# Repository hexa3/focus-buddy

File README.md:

# Focus Buddy

An e-ink Pomodoro companion for your desk. A little tomato with a face counts down your focus blocks on a
2.9" e-paper screen, chimes when you're done, and naps when you walk away.

- **Seeed XIAO ESP32-C3** + **Waveshare 2.9" e-paper** (296×128)
- 3 buttons, buzzer, optional LiPo with battery gauge
- **All through-hole**, 18 parts, about 2 h to build
- Light sleep between screen updates; deep sleep (≈0.05 mA) after 3 min idle. E-ink keeps the image with zero power.

## Pictures

> No unit has been built yet, so these aren't photos. Each one comes straight from the project files:
> KiCad renders and exports, the real enclosure geometry, and screens drawn by the actual firmware in the desktop simulator.

**The screens:** every state, drawn by `firmware/src/ui.cpp`

**The PCB:** 106 × 64 mm, 2 layers, all through-hole (KiCad 3D render)

**Routing:** back copper layer, seen from behind (KiCad export)

**The case:** front shell, PCB, back cover and button caps, exploded (rendered from the OpenSCAD model)

**The schematic** (KiCad export)

**The buddy talks:** speech bubble added in the latest display update (before / after, real firmware output)

## What's in here

This repo holds **source files only**. Gerbers, STLs, STEP, PDFs, renders and videos are generated from them
(see "Generate the outputs" below) and are not committed.

| Path | What |
|---|---|
| [`docs/BUILD.md`](docs/BUILD.md) | **Start here.** Ordering, printing, soldering, flashing, assembly, troubleshooting |
| [`hardware/BOM.csv`](hardware/BOM.csv) | **Everything you need:** PCB parts, display, screws, printed parts, filament, solder, tools, software (generated by `tools/gen_bom.py`) |
| `tools/netlist.py` | **Single source of truth:** every part, net and its position on the board |
| `hardware/pcb/` | KiCad 9 project: `.kicad_pro`, `.kicad_sch`, `.kicad_pcb`, project symbol and footprint libraries |
| `hardware/cad/enclosure.scad` | Parametric OpenSCAD source of the case (front shell, back cover, button caps, stand) |
| `hardware/cad/pcb_positions.scad` | Hole and switch positions taken from the PCB (generated by `tools/gen_cad_params.py`) |
| `firmware/` | PlatformIO firmware (Arduino/ESP32, GxEPD2). All screen drawing is in `src/ui.cpp` |
| `sim/` | Desktop simulator: compiles `ui.cpp` for your PC and renders the real screens |
| `tools/` | `build_pcb.py` (place + ground pour), `route_pcb.py` (A* autorouter), `build_schematic.py`, `gen_bom.py`, `gen_cad_params.py`, `render_stl.py`, `make_all.sh` |
| `video/` | Scripts that render the progress reels and before/after clips from simulator output |

## Generate the outputs

```bash
tools/make_all.sh
```

This needs Docker (it uses the `kicad/kicad:9.0` and `openscad/openscad:2021.01` images) and runs at low priority on 1 CPU.
It writes:

| Output | Path |
|---|---|
| Gerbers + drill files (upload the zip to a PCB fab) | `hardware/fab/focus-buddy-gerbers.zip` |
| Schematic PDF | `hardware/fab/focus-buddy-schematic.pdf` |
| PCB STEP model, 3D renders, part positions | `hardware/fab/` |
| Printable STLs | `hardware/cad/stl/` |
| DRC / ERC reports | `hardware/pcb/*.rpt` |

## Quick start

```bash
# 1. firmware
cd firmware && pio run -t upload

# 2. preview the screens without hardware
pio run                       # once, to fetch the graphics library
../sim/build.sh
../sim/fbsim main 1 0 1 1380000 1500000 2 2 37 0 3900 "Classic 25/5" 25 /tmp/screen.pbm

# 3. regenerate all hardware outputs (docker; low priority, 1 CPU)
tools/make_all.sh
```

## Verification status

| Check | Result |
|---|---|
| Firmware build, 4 panel variants | ✅ compiles (≈23 % flash, 6 % RAM) |
| Schematic ERC | ✅ 0 errors |
| PCB DRC | ✅ 0 errors, 0 unconnected |
| Schematic ↔ PCB parity | ✅ 0 issues |
| Enclosure STLs | ✅ manifold (OpenSCAD "Simple: yes") |
| **Built and tested on real hardware** | ❌ **not yet.** Rev A is unbuilt; see the checklist in BUILD.md |

The repo-wide DRC/ERC reports also list "library not in global table" notes. Those come from the bare docker
image used for CI, not from the design.

## License

Suggested: hardware CERN-OHL-P v2, firmware and tools MIT. These were picked as sensible open defaults; change them before publishing if you prefer something else.

---

<p align="center"><sub><i>Disclaimer: this README was generated by AI. I'm honestly terrible at describing my own projects (my first draft is usually just "it does the thing, trust me"), so I let a robot do the explaining.</i></sub></p>

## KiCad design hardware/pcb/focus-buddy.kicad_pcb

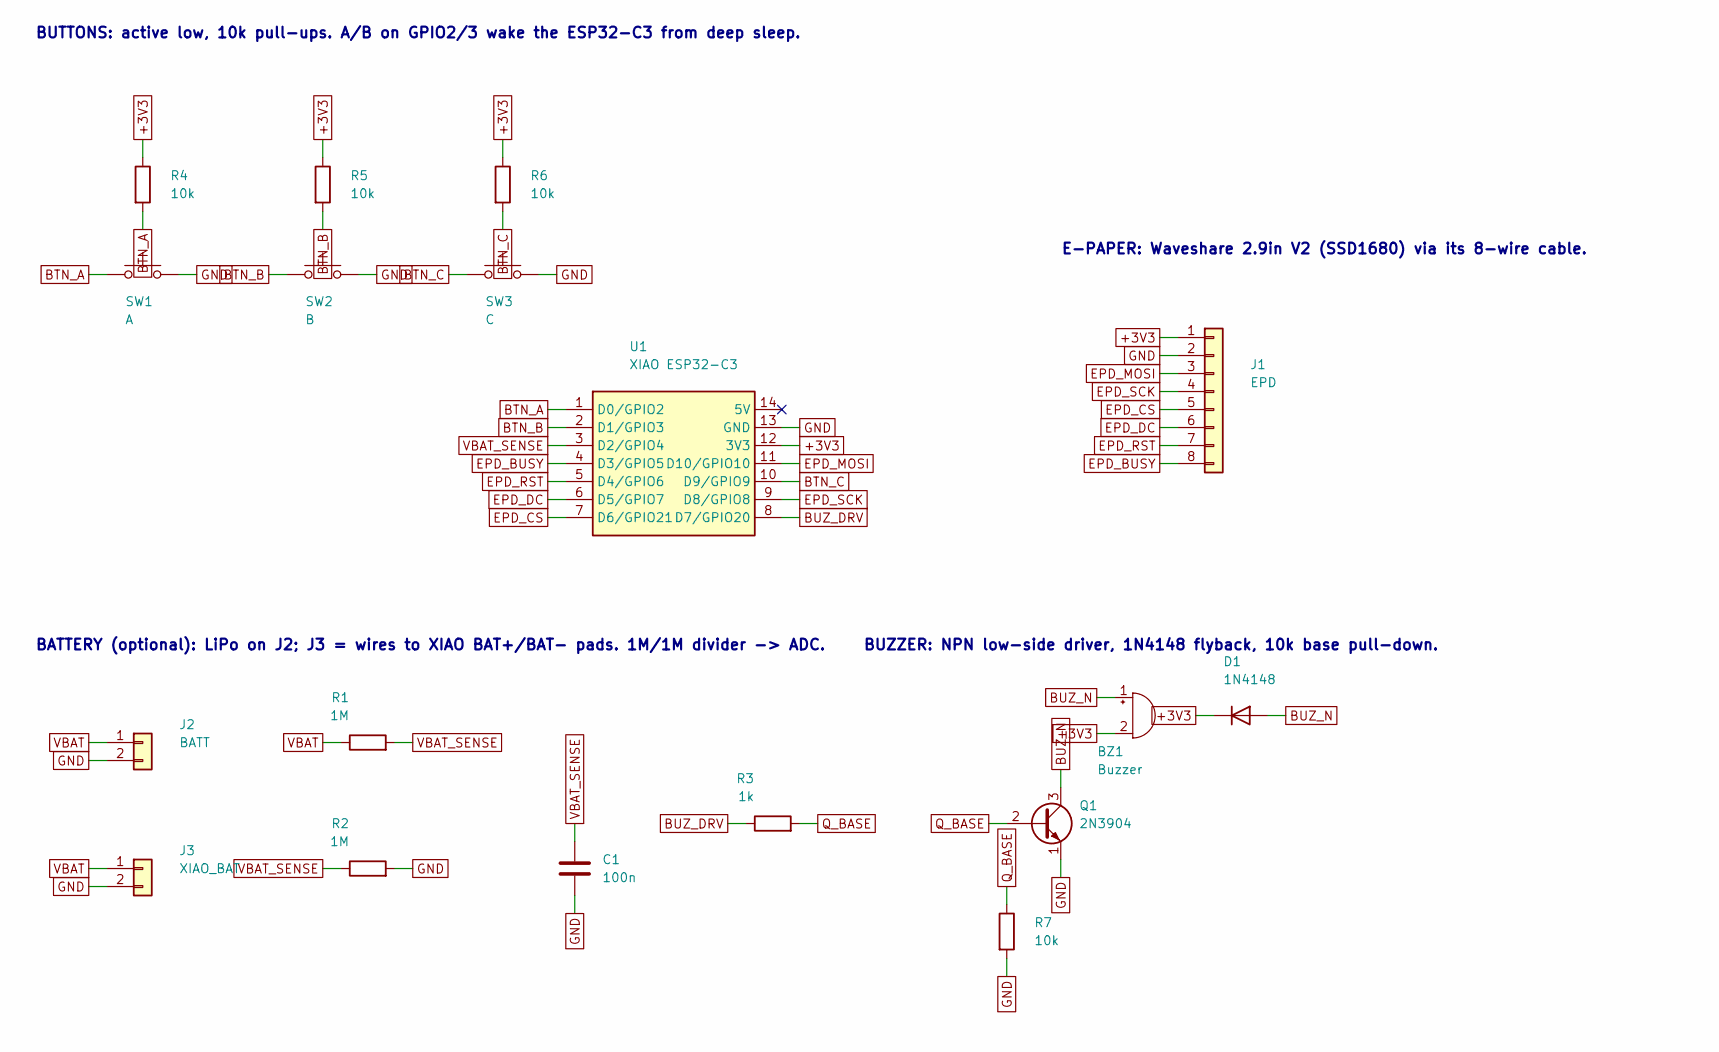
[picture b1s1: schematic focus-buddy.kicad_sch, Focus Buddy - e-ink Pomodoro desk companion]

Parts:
BZ1: Buzzer; Buzzer_12x9.5RM7.6
C1: 100n; C_Disc_D5.0mm_W2.5mm_P5.00mm
D1: 1N4148; D_DO-35_SOD27_P7.62mm_Horizontal
J1: EPD; PinHeader_1x08_P2.54mm_Vertical
J2: BATT; JST_PH_B2B-PH-K_1x02_P2.00mm_Vertical
J3: XIAO_BAT; PinHeader_1x02_P2.54mm_Vertical
Q1: 2N3904; TO-92_Inline_Wide
R1, R2: 1M; R_Axial_DIN0207_L6.3mm_D2.5mm_P7.62mm_Horizontal
R3: 1k; R_Axial_DIN0207_L6.3mm_D2.5mm_P7.62mm_Horizontal
R4, R5, R6, R7: 10k; R_Axial_DIN0207_L6.3mm_D2.5mm_P7.62mm_Horizontal
SW1: A; SW_PUSH_6mm_H9.5mm
SW2: B; SW_PUSH_6mm_H9.5mm
SW3: C; SW_PUSH_6mm_H9.5mm
U1: XIAO ESP32-C3; Seeed_XIAO_THT

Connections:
+3V3: BZ1.2 (-), D1.1 (K), J1.1, R4.1, R5.1, R6.1, U1.12 (3V3)
BTN_A: R4.2, SW1.1, U1.1 (D0/GPIO2)
BTN_B: R5.2, SW2.1, U1.2 (D1/GPIO3)
BTN_C: R6.2, SW3.1, U1.10 (D9/GPIO9)
BUZ_DRV: R3.1, U1.8 (D7/GPIO20)
BUZ_N: BZ1.1 (+), D1.2 (A), Q1.3 (C)
EPD_BUSY: J1.8, U1.4 (D3/GPIO5)
EPD_CS: J1.5, U1.7 (D6/GPIO21)
EPD_DC: J1.6, U1.6 (D5/GPIO7)
EPD_MOSI: J1.3, U1.11 (D10/GPIO10)
EPD_RST: J1.7, U1.5 (D4/GPIO6)
EPD_SCK: J1.4, U1.9 (D8/GPIO8)
GND: C1.2, J1.2, J2.2, J3.2, Q1.1 (E), R2.2, R7.2, SW1.2, SW2.2, SW3.2, U1.13 (GND)
Q_BASE: Q1.2 (B), R3.2, R7.1
VBAT: J2.1, J3.1, R1.1
VBAT_SENSE: C1.1, R1.2, R2.1, U1.3 (D2/GPIO4)

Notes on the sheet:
BUTTONS: active low, 10k pull-ups. A/B on GPIO2/3 wake the ESP32-C3 from deep sleep.
BATTERY (optional): LiPo on J2; J3 = wires to XIAO BAT+/BAT- pads. 1M/1M divider -> ADC.
BUZZER: NPN low-side driver, 1N4148 flyback, 10k base pull-down.
E-PAPER: Waveshare 2.9in V2 (SSD1680) via its 8-wire cable.

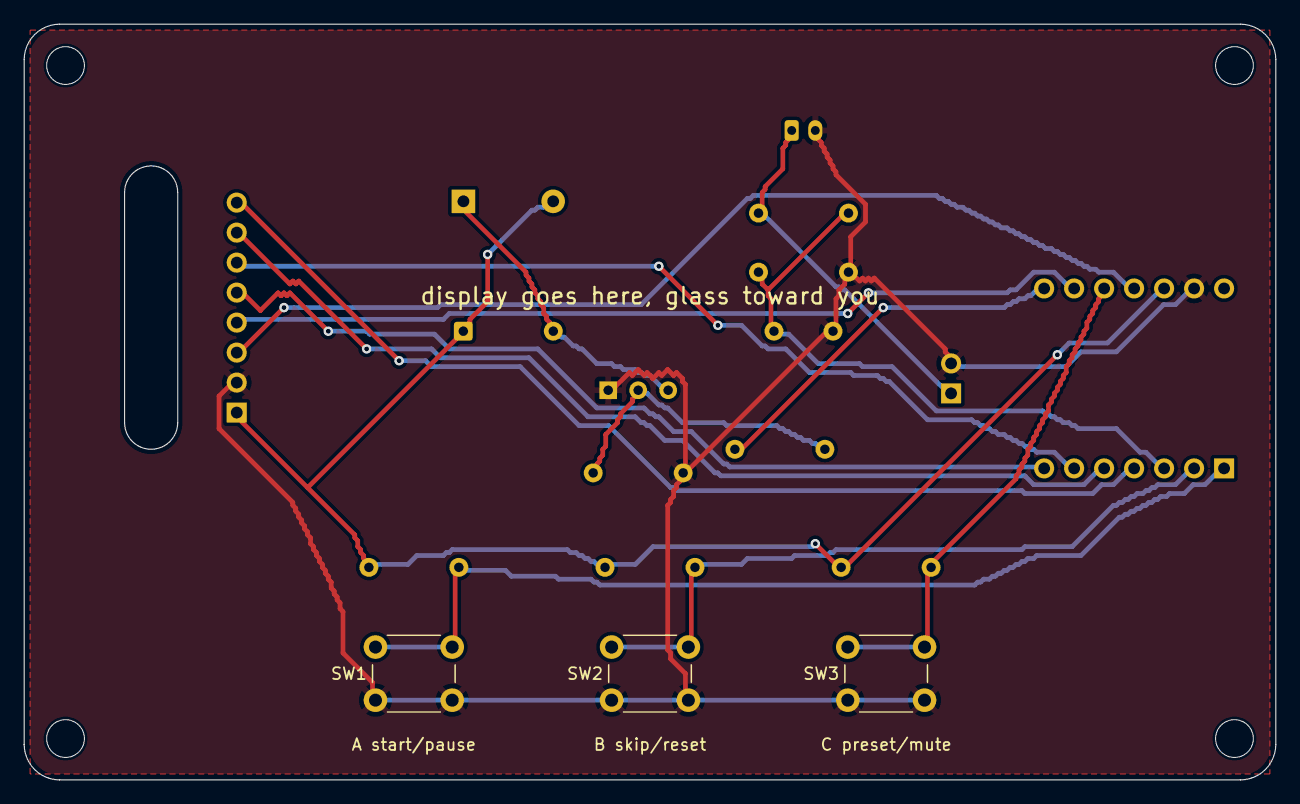
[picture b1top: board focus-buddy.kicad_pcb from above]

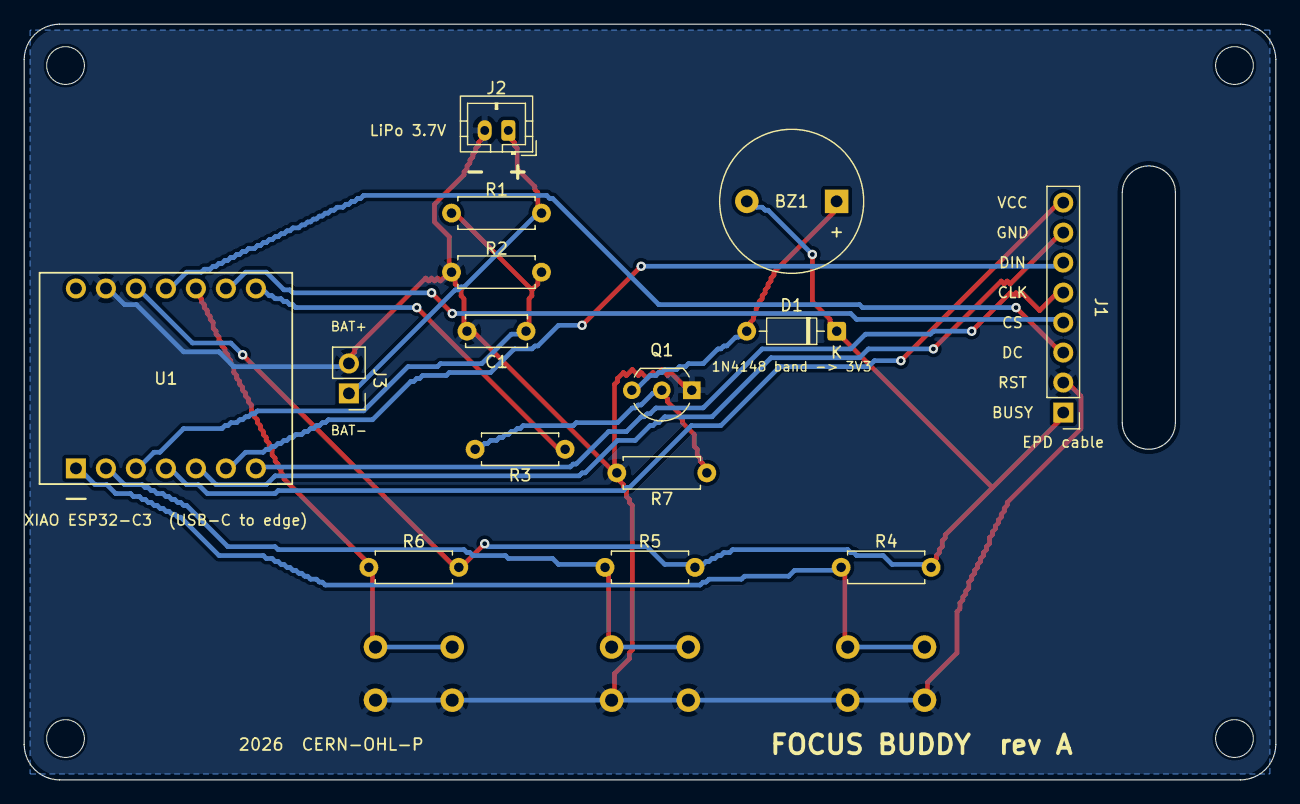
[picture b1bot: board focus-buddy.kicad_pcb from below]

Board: 2 copper layers, 106.0 x 64.0 mm, 22 parts (15 on the bottom side), 16 nets.

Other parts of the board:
H1, H2, H3, H4: MountingHole_3.2mm_M3

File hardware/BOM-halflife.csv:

Item,Qty,Supplier,Cost/item,Total Cost,link
Seeed Studio XIAO ESP32-C3,1,Seeed Studio,$4.90,$4.90,https://www.seeedstudio.com/Seeed-XIAO-ESP32C3-p-5431.html
"2.9"" e-paper module, Waveshare V2",1,Waveshare,$21.99,$21.99,https://www.waveshare.com/2.9inch-e-paper-module.htm
"Printed circuit board (5 pcs, 106x64 mm, 2 layer): paste JLCPCB quote",1,JLCPCB,quote,quote,https://jlcpcb.com/quote
"Tactile switch 6x6 mm, 9.5 mm tall, through-hole",3,Tayda Electronics,$0.040,$0.12,https://www.taydaelectronics.com/tact-switch-6x6mm-9-5mm-thr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
Resistor 10 kΩ,4,Tayda Electronics,$0.015,$0.06,https://www.taydaelectronics.com/resistors/1-4w-metal-film-r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
Resistor 1 MΩ,2,Tayda Electronics,$0.015,$0.03,https://www.taydaelectronics.com/resistors/1-4w-metal-film-r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
Resistor 1 kΩ,1,Tayda Electronics,$0.015,$0.01,https://www.taydaelectronics.com/resistors/1-4w-metal-film-r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
"NPN transistor 2N3904, TO-92",1,Futurlec,$0.060,$0.06,https://www.futurlec.com/Transistors/2N3904pr.shtml
Diode 1N4148,1,Tayda Electronics,$0.020,$0.02,
"Buzzer 12 mm, 3 V, 7.6 mm pin spacing",1,Tayda Electronics,$0.50,$0.50,
Capacitor 100 nF ceramic,1,Tayda Electronics,$0.020,$0.02,
"Pin header 1x8 male, 2.54 mm",1,Tayda Electronics,$0.050,$0.05,
"Male pin header 1x7, 2.54 mm",2,Tayda Electronics,$0.050,$0.10,
"JST-PH 2-pin socket, vertical (B2B-PH-K)",1,Tayda Electronics,$0.10,$0.10,
LiPo battery 3.7 V,1,Any,$5.00,$5.00,
Screw M3 x 20 mm,4,Any hardware store,$0.10,$0.40,
Double-sided foam tape,1,Any,$1.00,$1.00,
PLA or PETG filament,1,Any,$2.20,$2.20,
Estimated total shipping,1,,,$0.00,

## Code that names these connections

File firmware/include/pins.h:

#pragma once
// Focus Buddy rev A, Seeed XIAO ESP32-C3 pin map.
// Must match hardware/pcb (netlist in tools/netlist.py).

// Buttons: active LOW, 10k external pull-ups on the PCB.
// A and B are on GPIO2/3 so they can wake the chip from deep sleep (only GPIO0-5 can).
#define PIN_BTN_A      2   // D0  left   : start / pause / resume
#define PIN_BTN_B      3   // D1  middle : skip phase (hold = reset)
#define PIN_BTN_C      9   // D9  right  : preset (idle) / mute (running). This is also BOOT.

#define PIN_VBAT_SENSE 4   // D2  1M/1M divider from battery +
#define PIN_BUZZER    20   // D7  drives an NPN, buzzer between 3V3 and the collector

// E-paper (SPI, write only)
#define PIN_EPD_BUSY   5   // D3
#define PIN_EPD_RST    6   // D4
#define PIN_EPD_DC     7   // D5
#define PIN_EPD_CS    21   // D6
#define PIN_EPD_SCK    8   // D8
#define PIN_EPD_MOSI  10   // D10

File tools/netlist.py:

"""Focus Buddy rev A: single source of truth for parts, nets and placement.

Used by build_pcb.py (runs inside the kicad/kicad:9.0 docker image) and by
build_schematic.py. Coordinates are board millimetres, origin = top-left
corner of the PCB *seen from the front* (the side facing the user), y down.

Sides:
  F = front (user-facing, behind the display): only the three buttons
  B = back  (inside the case): everything else
"""

BOARD_W, BOARD_H = 106.0, 64.0
CORNER_R = 3.0
MOUNT_HOLES = [(3.5, 3.5), (102.5, 3.5), (3.5, 60.5), (102.5, 60.5)]
# slot for the display cable to pass from the front to the back
CABLE_SLOT = (8.5, 12.0, 13.0, 36.0)  # x0, y0, x1, y1
# where the e-paper module sits in front of the board (for the CAD model)
DISPLAY_MODULE = dict(cx=53.0, cy=23.0, w=89.5, h=38.0)

KLIB = "/usr/share/kicad/footprints/"

# ref: (value, footprint "Lib:Name", center x, center y, rotation deg, side, {pad: net}, description, LCSC/part hint)
PARTS = {
    "U1":  ("XIAO ESP32-C3", "focusbuddy:Seeed_XIAO_THT", 94.0, 30.0, 0, "B",
            {"1": "BTN_A", "2": "BTN_B", "3": "VBAT_SENSE", "4": "EPD_BUSY", "5": "EPD_RST",
             "6": "EPD_DC", "7": "EPD_CS", "8": "BUZ_DRV", "9": "EPD_SCK", "10": "BTN_C",
             "11": "EPD_MOSI", "12": "+3V3", "13": "GND", "14": "unconnected-(U1-5V-Pad14)"},
            "Seeed Studio XIAO ESP32-C3 (with antenna), soldered on 2x 1x7 male headers", "Seeed XIAO ESP32C3"),
    "J1":  ("EPD", "Connector_PinHeader_2.54mm:PinHeader_1x08_P2.54mm_Vertical", 18.0, 24.0, 0, "B",
            {"1": "+3V3", "2": "GND", "3": "EPD_MOSI", "4": "EPD_SCK", "5": "EPD_CS",
             "6": "EPD_DC", "7": "EPD_RST", "8": "EPD_BUSY"},
            "1x8 2.54 mm male header, display cable (VCC GND DIN CLK CS DC RST BUSY)", "2.54mm 1x8 male header"),
    "J2":  ("BATT", "Connector_JST:JST_PH_B2B-PH-K_1x02_P2.00mm_Vertical", 66.0, 9.0, 0, "B",
            {"1": "VBAT", "2": "GND"},
            "JST-PH 2-pin vertical, optional 3.7 V LiPo (CHECK POLARITY)", "JST B2B-PH-K-S"),
    "J3":  ("XIAO_BAT", "Connector_PinHeader_2.54mm:PinHeader_1x02_P2.54mm_Vertical", 78.5, 30.0, 0, "B",
            {"1": "VBAT", "2": "GND"},
            "2 solder holes: wires to the XIAO BAT+/BAT- pads (only if using a battery)", "-"),
    "BZ1": ("Buzzer", "Buzzer_Beeper:Buzzer_12x9.5RM7.6", 41.0, 15.0, 0, "B",
            {"1": "BUZ_N", "2": "+3V3"},
            "12 mm passive/magnetic buzzer 3 V, 7.6 mm pin spacing", "12x9.5mm 3V passive buzzer 7.6mm"),
    "Q1":  ("2N3904", "Package_TO_SOT_THT:TO-92_Inline_Wide", 52.0, 31.0, 0, "B",
            {"1": "GND", "2": "Q_BASE", "3": "BUZ_N"},
            "NPN transistor TO-92 (2N3904 / S8050 / BC337, EBC pinout)", "2N3904 TO-92"),
    "D1":  ("1N4148", "Diode_THT:D_DO-35_SOD27_P7.62mm_Horizontal", 41.0, 26.0, 0, "B",
            {"1": "+3V3", "2": "BUZ_N"},
            "1N4148 flyback diode (cathode band to +3V3)", "1N4148 DO-35"),
    "R1":  ("1M", "Resistor_THT:R_Axial_DIN0207_L6.3mm_D2.5mm_P7.62mm_Horizontal", 66.0, 16.0, 0, "B",
            {"1": "VBAT", "2": "VBAT_SENSE"}, "1 MΩ 1/4 W, battery divider top", "-"),
    "R2":  ("1M", "Resistor_THT:R_Axial_DIN0207_L6.3mm_D2.5mm_P7.62mm_Horizontal", 66.0, 21.0, 0, "B",
            {"1": "VBAT_SENSE", "2": "GND"}, "1 MΩ 1/4 W, battery divider bottom", "-"),
    "C1":  ("100n", "Capacitor_THT:C_Disc_D5.0mm_W2.5mm_P5.00mm", 66.0, 26.0, 0, "B",
            {"1": "VBAT_SENSE", "2": "GND"}, "100 nF ceramic, ADC filter", "-"),
    "R3":  ("1k", "Resistor_THT:R_Axial_DIN0207_L6.3mm_D2.5mm_P7.62mm_Horizontal", 64.0, 36.0, 0, "B",
            {"1": "BUZ_DRV", "2": "Q_BASE"}, "1 kΩ base resistor", "-"),
    "R7":  ("10k", "Resistor_THT:R_Axial_DIN0207_L6.3mm_D2.5mm_P7.62mm_Horizontal", 52.0, 38.0, 0, "B",
            {"1": "Q_BASE", "2": "GND"}, "10 kΩ base pull-down (keeps buzzer off at boot)", "-"),
    "R4":  ("10k", "Resistor_THT:R_Axial_DIN0207_L6.3mm_D2.5mm_P7.62mm_Horizontal", 33.0, 46.0, 0, "B",
            {"1": "+3V3", "2": "BTN_A"}, "10 kΩ pull-up button A", "-"),
    "R5":  ("10k", "Resistor_THT:R_Axial_DIN0207_L6.3mm_D2.5mm_P7.62mm_Horizontal", 53.0, 46.0, 0, "B",
            {"1": "+3V3", "2": "BTN_B"}, "10 kΩ pull-up button B", "-"),
    "R6":  ("10k", "Resistor_THT:R_Axial_DIN0207_L6.3mm_D2.5mm_P7.62mm_Horizontal", 73.0, 46.0, 0, "B",
            {"1": "+3V3", "2": "BTN_C"}, "10 kΩ pull-up button C", "-"),
    "SW1": ("A", "Button_Switch_THT:SW_PUSH_6mm_H9.5mm", 33.0, 55.0, 0, "F",
            {"1": "BTN_A", "2": "GND"}, "6x6 mm tactile switch, 9.5 mm tall", "6x6x9.5mm tactile switch THT"),
    "SW2": ("B", "Button_Switch_THT:SW_PUSH_6mm_H9.5mm", 53.0, 55.0, 0, "F",
            {"1": "BTN_B", "2": "GND"}, "6x6 mm tactile switch, 9.5 mm tall", "6x6x9.5mm tactile switch THT"),
    "SW3": ("C", "Button_Switch_THT:SW_PUSH_6mm_H9.5mm", 73.0, 55.0, 0, "F",
            {"1": "BTN_C", "2": "GND"}, "6x6 mm tactile switch, 9.5 mm tall", "6x6x9.5mm tactile switch THT"),
}

XIAO_PIN_NAMES = {
    "1": "D0/GPIO2", "2": "D1/GPIO3", "3": "D2/GPIO4", "4": "D3/GPIO5", "5": "D4/GPIO6",
    "6": "D5/GPIO7", "7": "D6/GPIO21", "8": "D7/GPIO20", "9": "D8/GPIO8", "10": "D9/GPIO9",
    "11": "D10/GPIO10", "12": "3V3", "13": "GND", "14": "5V",
}


def nets():
    """net name -> list of (ref, pad)"""
    out = {}
    for ref, p in PARTS.items():
        for pad, net in p[6].items():
            out.setdefault(net, []).append((ref, pad))
    return out


if __name__ == "__main__":
    for n, conns in sorted(nets().items()):
        print(f"{n:12s} {' '.join(f'{r}.{p}' for r, p in conns)}")

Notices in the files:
hardware/pcb/focus-buddy.kicad_pcb:
open hardware, CERN-OHL-P
2026  CERN-OHL-P
